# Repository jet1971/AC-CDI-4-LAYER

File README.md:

# AC-CDI-4-layer
# AC-CDI-4-layer

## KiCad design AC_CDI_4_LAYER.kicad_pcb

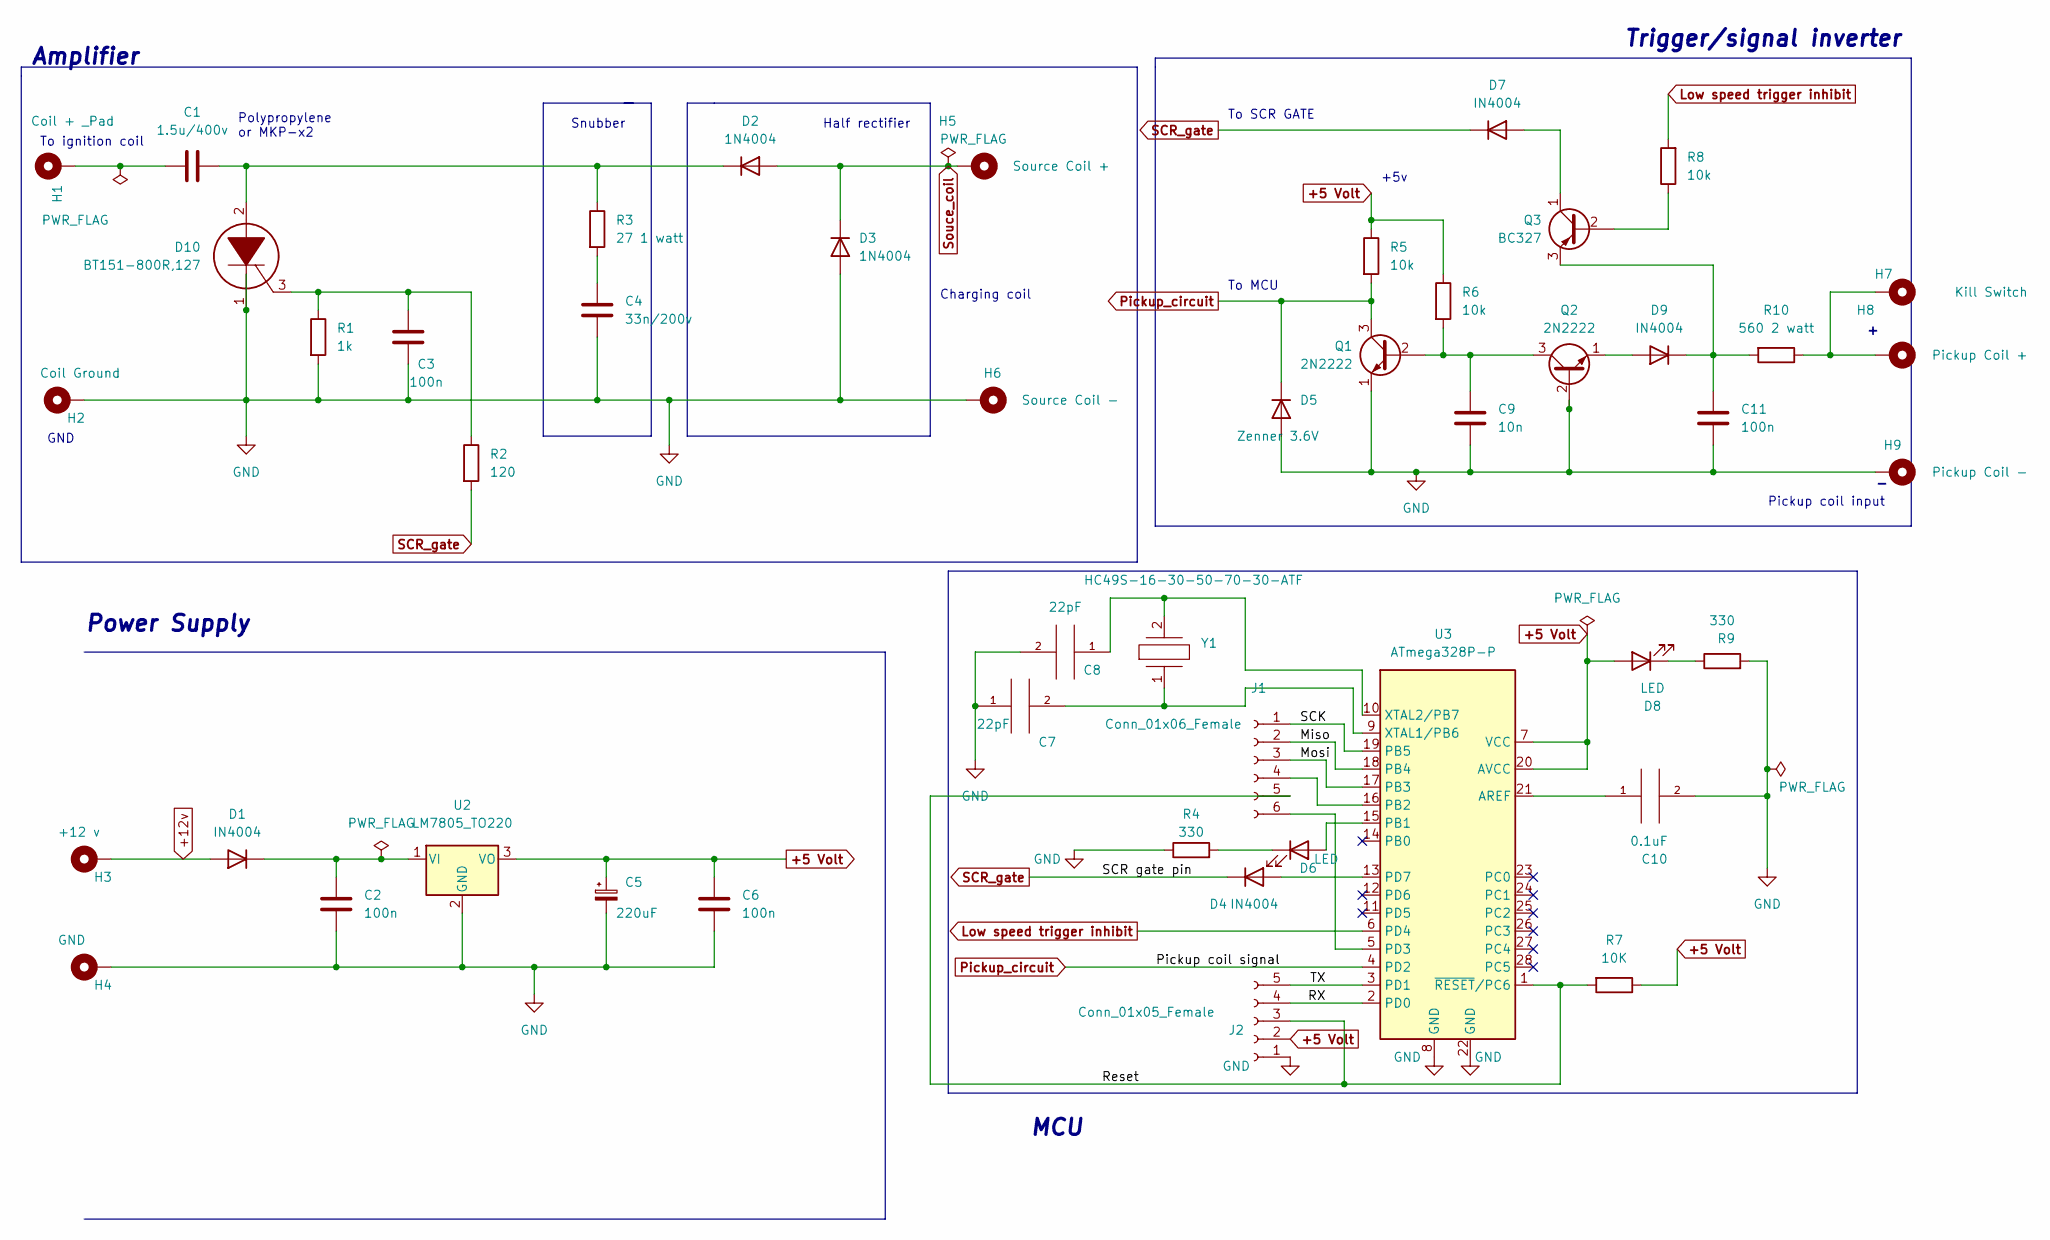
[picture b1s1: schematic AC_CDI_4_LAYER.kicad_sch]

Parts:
C1: 1.5u/400v; C_Rect_L26.5mm_W5.0mm_P22.50mm_MKS4
C2, C3, C6, C11: 100n; C_Disc_D6.0mm_W2.5mm_P5.00mm
C4: 33n/200v; C_Rect_L9.0mm_W3.2mm_P7.50mm_MKT
C5: 220uF; CP_Radial_D10.0mm_P3.50mm
C7, C8: 22pF; C_Disc_D5.0mm_W2.5mm_P5.00mm
C9: 10n; C_Disc_D6.0mm_W2.5mm_P5.00mm
C10: 0.1uF; C_Disc_D6.0mm_W2.5mm_P5.00mm
D1, D7, D9: IN4004; D_DO-41_SOD81_P7.62mm_Horizontal
D2, D3: 1N4004; D_DO-41_SOD81_P10.16mm_Horizontal
D4: IN4004; D_DO-41_SOD81_P10.16mm_Horizontal
D5: Zenner 3.6V; D_DO-41_SOD81_P7.62mm_Horizontal
D6, D8: LED; LED_D3.0mm
D10: BT151-800R,127; TO254P470X1000X2000-3P; Manufacturer_Part_Number BT151-800R,127; Mouser Part Number 771-BT151-800R127
H1: Coil + _Pad; MountingHole_2.2mm_M2_ISO14580_Pad_TopBottom
H2: Coil Ground; MountingHole_2.2mm_M2_Pad_TopBottom
H3: +12 v; MountingHole_2.2mm_M2_Pad_TopBottom
H4: GND; MountingHole_2.2mm_M2_Pad_TopBottom
H5: Source Coil +; MountingHole_2.2mm_M2_Pad_TopBottom
H6: Source Coil -; MountingHole_2.2mm_M2_Pad_TopBottom
H7: Kill Switch; MountingHole_2.2mm_M2_Pad_TopBottom
H8: Pickup Coil +; MountingHole_2.2mm_M2_Pad_TopBottom
H9: Pickup Coil -; MountingHole_2.2mm_M2_Pad_TopBottom
J1: Conn_01x06_Female; PinSocket_1x06_P2.54mm_Vertical
J2: Conn_01x05_Female; PinSocket_1x05_P2.54mm_Vertical
Q1, Q2: 2N2222; TO-92_Inline
Q3: BC327; TO-92_Inline
R1: 1k; R_Axial_DIN0207_L6.3mm_D2.5mm_P10.16mm_Horizontal
R2: 120; R_Axial_DIN0207_L6.3mm_D2.5mm_P10.16mm_Horizontal
R3: 27 1 watt; R_Axial_DIN0516_L15.5mm_D5.0mm_P20.32mm_Horizontal
R4, R9: 330; R_Axial_DIN0207_L6.3mm_D2.5mm_P10.16mm_Horizontal
R5, R6, R8: 10k; R_Axial_DIN0207_L6.3mm_D2.5mm_P10.16mm_Horizontal
R7: 10K; R_Axial_DIN0207_L6.3mm_D2.5mm_P10.16mm_Horizontal
R10: 560 2 watt; R_Axial_DIN0516_L15.5mm_D5.0mm_P20.32mm_Horizontal
U2: LM7805_TO220; TO-220-3_Vertical
U3: ATmega328P-P; DIP-28_W7.62mm
Y1: HC49S-16-30-50-70-30-ATF; Resonator-2Pin_W8.0mm_H3.5mm; Manufacturer_Part_Number HC49S-16-30-50-70-30-ATF

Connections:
+5 Volt: C5.1, C6.1, D8.2 (A), J2.2, R5.1, R6.1, R7.1, U2.3 (VO), U3.7 (VCC), U3.20 (AVCC)
+12v: D1.2 (A), H3.1
/Miso: J1.2, U3.18 (PB4)
/Mosi: J1.3, U3.17 (PB3)
/RX: J2.4, U3.2 (PD0)
/Reset: J1.5, J2.3, R7.2, U3.1 (~RESET/PC6)
/SCK: J1.1, U3.19 (PB5)
/TX: J2.5, U3.3 (PD1)
GND: C2.2, C3.2, C4.2, C5.2, C6.2, C7.1, C8.2, C9.2, C10.2, C11.2, D3.2 (A), D5.2 (A), D10.1, H2.1, H4.1, H6.1, H9.1, J2.1, Q1.1 (E), Q2.2 (B), R1.2, R4.1, R9.2, U2.2 (GND), U3.8 (GND), U3.22 (GND)
Low speed trigger inhibit: R8.2, U3.6 (PD4)
unnamed: C1.1, D2.1 (K), D10.2, R3.1
unnamed: C1.2, H1.1
unnamed: C2.1, D1.1 (K), U2.1 (VI)
unnamed: C3.1, D10.3, R1.1, R2.1
unnamed: C4.1, R3.2
unnamed: C7.2, U3.9 (XTAL1/PB6), Y1.1
unnamed: C8.1, U3.10 (XTAL2/PB7), Y1.2
unnamed: C9.1, Q1.2 (B), Q2.3 (C), R6.2
unnamed: C10.1, U3.21 (AREF)
unnamed: C11.1, D9.1 (K), Q3.3 (E), R10.2
unnamed: D4.2 (A), U3.13 (PD7)
unnamed: D6.1 (K), R4.2
unnamed: D6.2 (A), U3.15 (PB1)
unnamed: D7.2 (A), Q3.1 (C)
unnamed: D8.1 (K), R9.1
unnamed: D9.2 (A), Q2.1 (E)
unnamed: H7.1, H8.1, R10.1
unnamed: J1.4, U3.16 (PB2)
unnamed: J1.6, U3.5 (PD3)
unnamed: Q3.2 (B), R8.1
Pickup_circuit: D5.1 (K), Q1.3 (C), R5.2, U3.4 (PD2)
SCR_gate: D4.1 (K), D7.1 (K), R2.2
Souce_coil: D2.2 (A), D3.1 (K), H5.1

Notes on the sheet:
Power Supply
Pickup coil input
Charging coil
Snubber
GND
To SCR GATE
Trigger/signal inverter
MCU
Amplifier
Polypropylene or MKP-x2
To ignition coil
To MCU
+5v
Half rectifier

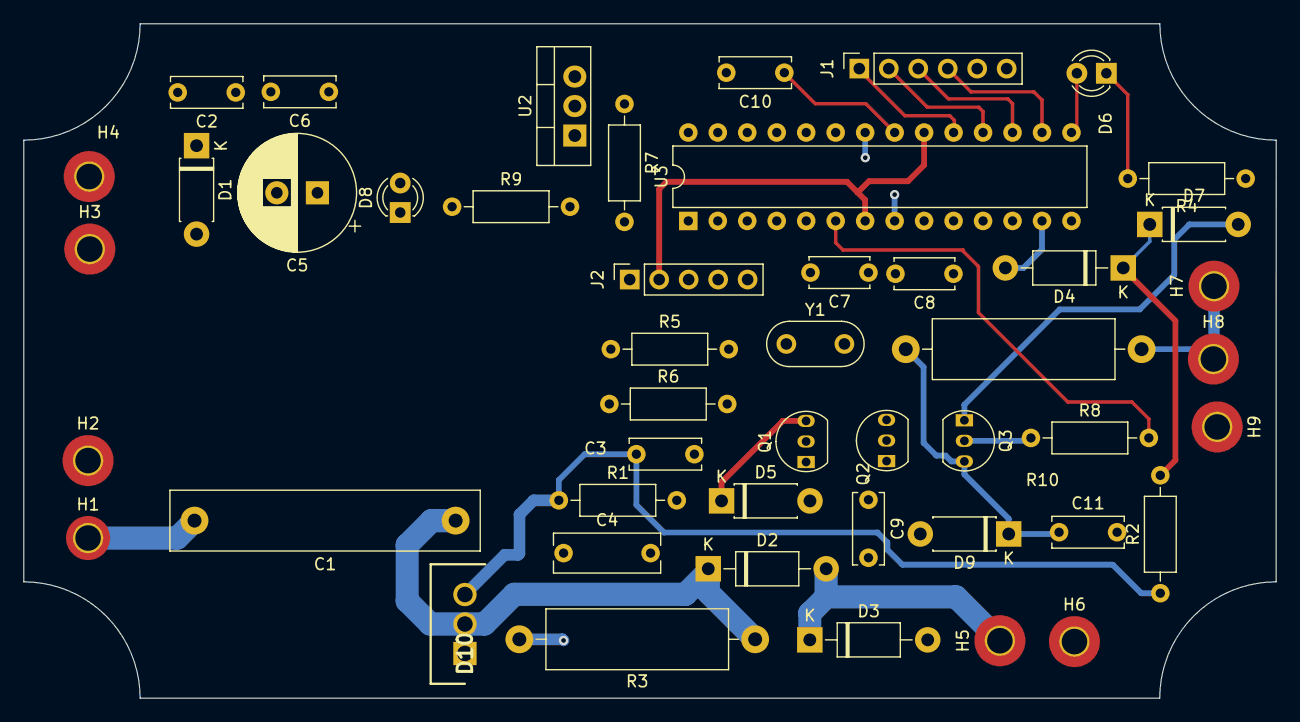
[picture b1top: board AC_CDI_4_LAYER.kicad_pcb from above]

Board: 4 copper layers, 107.9 x 58.1 mm, 48 parts (0 on the bottom side), 33 nets.

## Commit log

2022-11-02 4 layer first commit
